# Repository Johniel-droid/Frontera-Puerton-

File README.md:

Perspectiva del proyecto: FRONTERA será desarrollado como un proyecto con enfoque educativo, utilizando un portón automatizado como ejemplo práctico para aprender y aplicar conceptos de programación, máquinas de estados, control de motores y comunicación Wi-Fi. El sistema permitirá observar de manera práctica cómo interactúan el microcontrolador, sensores, actuadores y comunicación inalámbrica.

El Estudiante tendra el sentir de que esta aplicando inmediatamente lo que aprende.

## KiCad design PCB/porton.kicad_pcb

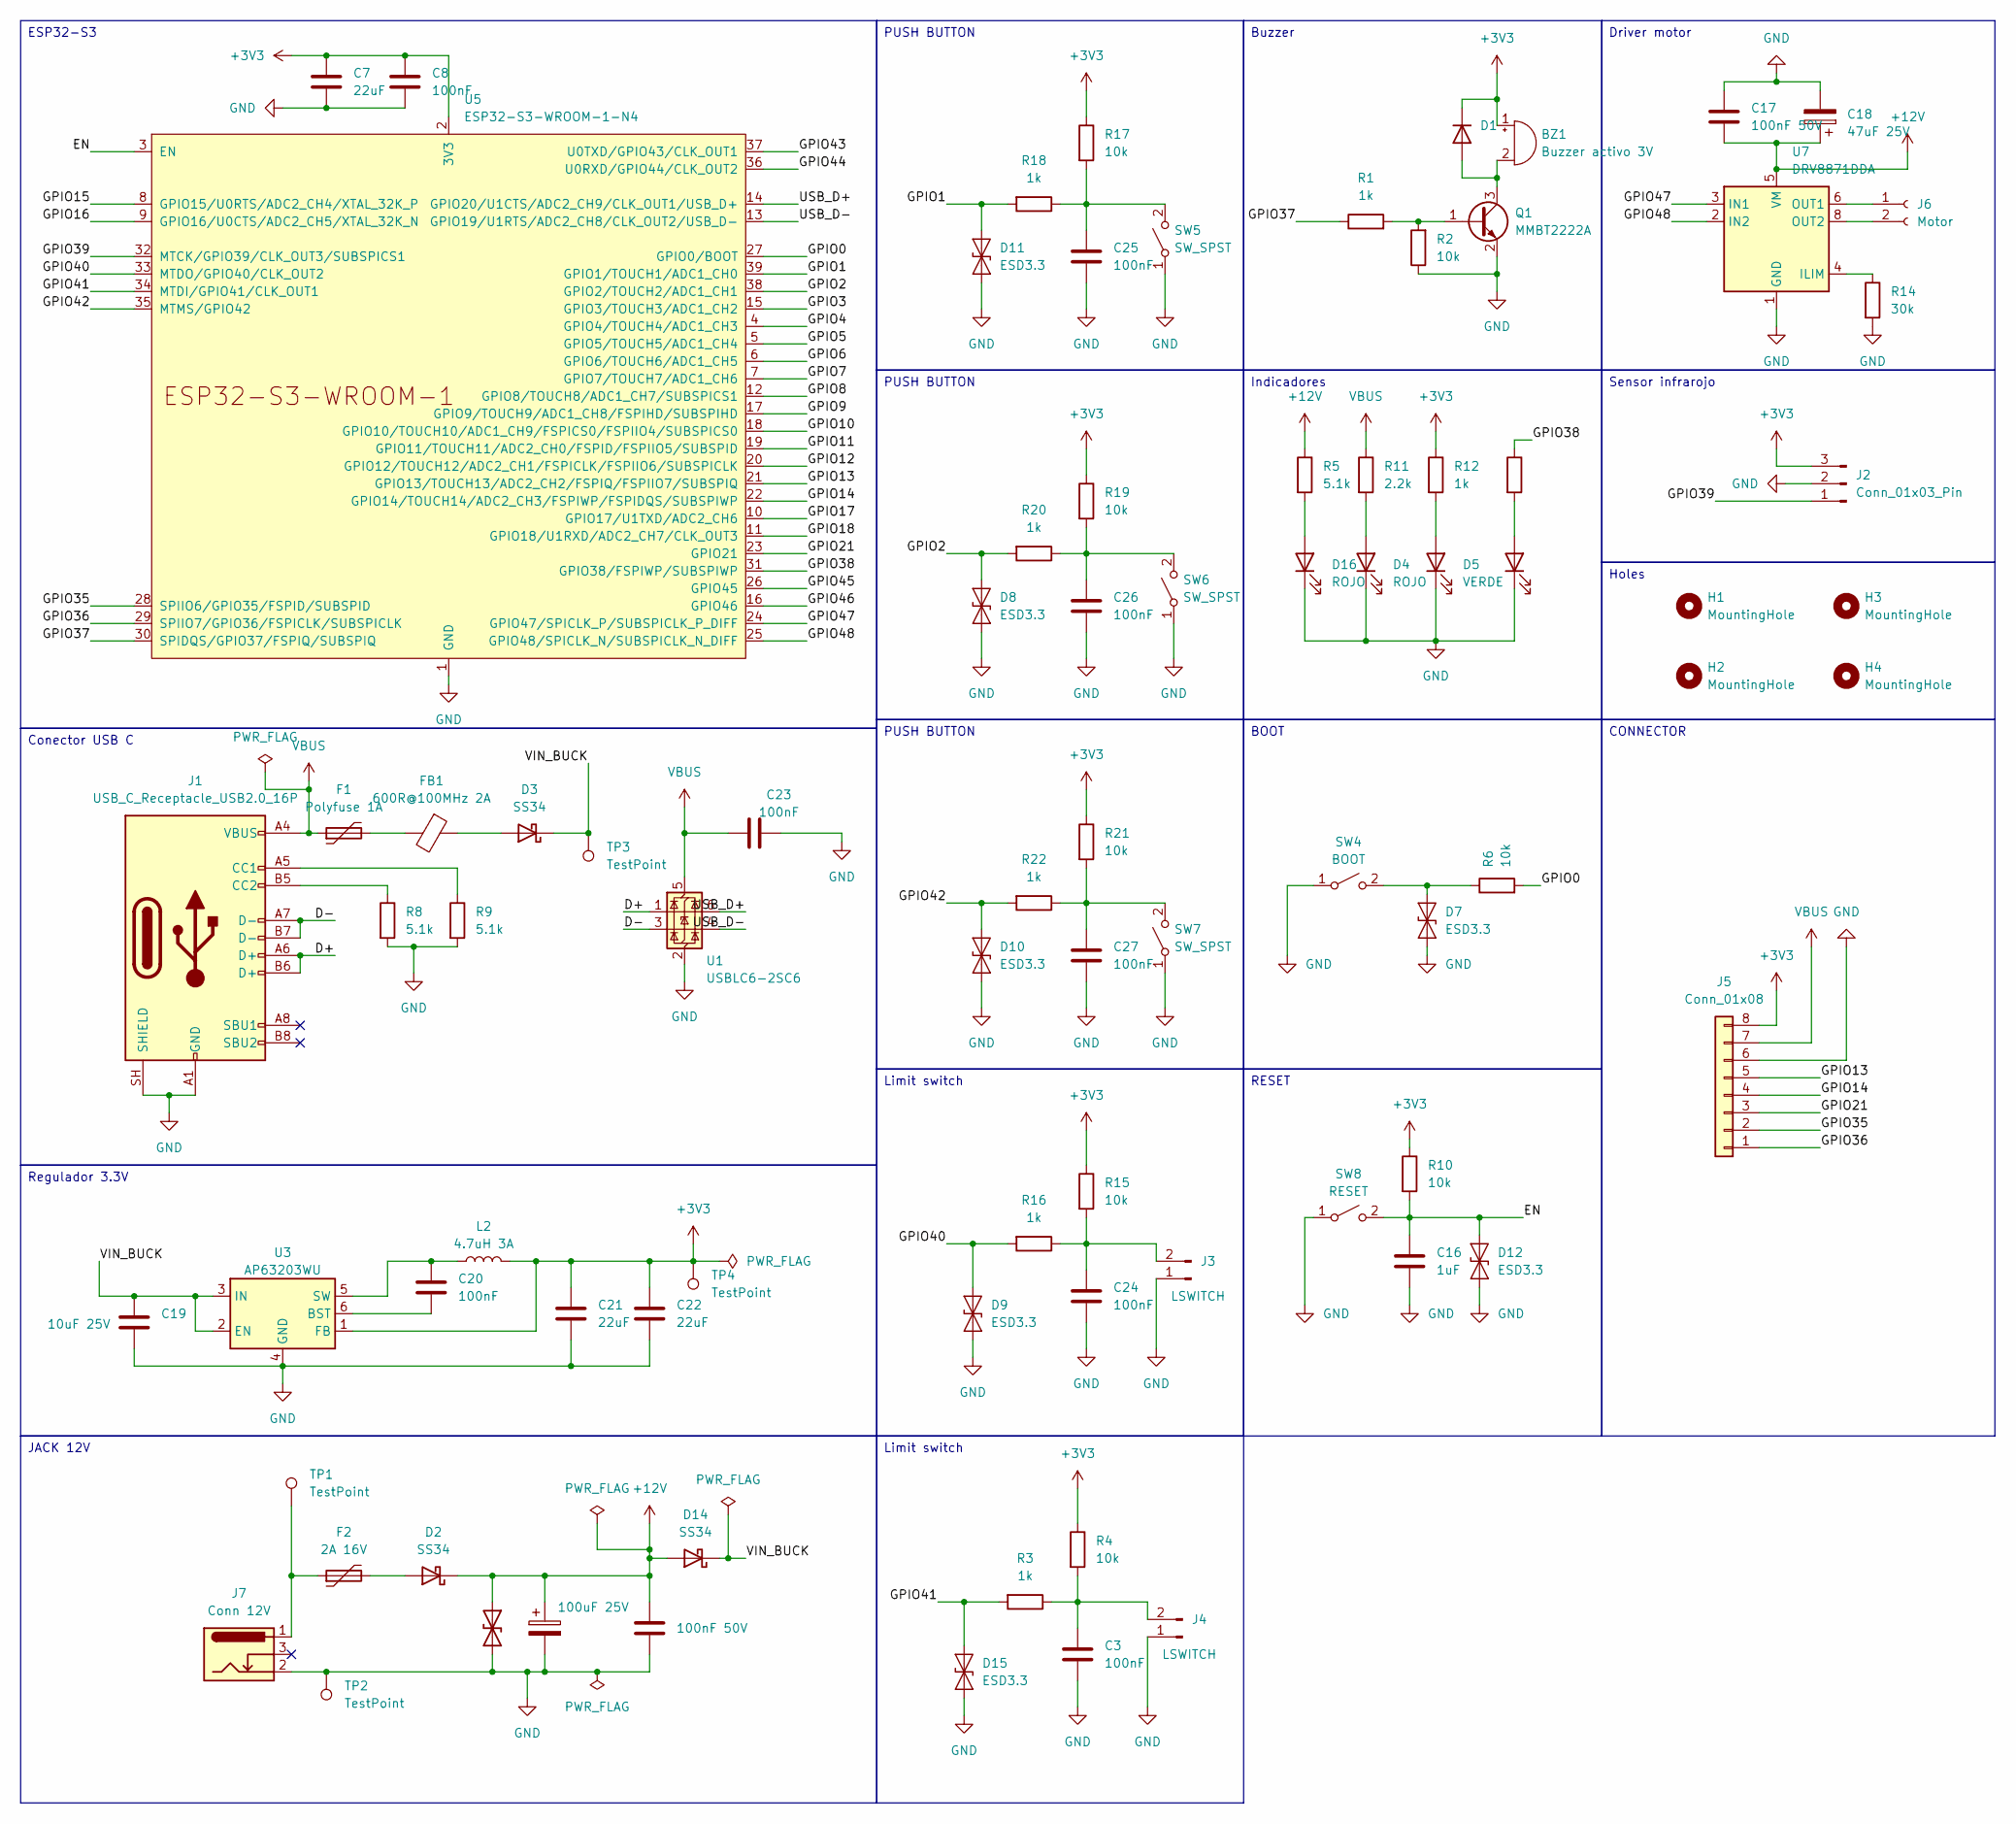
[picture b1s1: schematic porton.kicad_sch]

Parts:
BZ1: Buzzer activo 3V; Buzzer_12x9.5RM7.6; LCSC C252940
C1: 100uF 25V; CP_Elec_6.3x7.7; LCSC C3008501
C2: 100nF 50V; C_0805_2012Metric; LCSC C49678
C3, C8, C20, C24, C25, C26, C27: 100nF; C_0603_1608Metric; LCSC C14663
C7, C21, C22: 22uF; C_0805_2012Metric; LCSC C45783
C16: 1uF; C_0805_2012Metric; LCSC C28323
C17: 100nF 50V; C_0603_1608Metric; LCSC C14663
C18: 47uF 25V; CP_Elec_6.3x5.4; LCSC C2935117
C19: 10uF 25V; C_0805_2012Metric; LCSC C15850
C23: 100nF; C_0805_2012Metric; LCSC C49678
D1: 1N4148W; D_SOD-123; LCSC C81598
D2, D3, D14: SS34; D_SMA; LCSC C8678
D4, D16: ROJO; LED_0603_1608Metric; LCSC C2286
D5: VERDE; LED_0603_1608Metric; LCSC C72043
D6: Amarillo; LED_0603_1608Metric; LCSC C72038
D7, D8, D9, D10, D11, D12, D15: ESD3.3; D_SOD-923; LCSC C96512
D13: SMBJ15CA; D_SMB; LCSC C113989
F1: Polyfuse 1A; Fuse_1206_3216Metric; LCSC C883131
F2: 2A 16V; Fuse_1812_4532Metric; LCSC C18198340
FB1: 600R@100MHz 2A; L_0805_2012Metric; LCSC C21519
H1, H2, H3, H4: MountingHole; MountingHole_3.2mm_M3
J1: USB_C_Receptacle_USB2.0_16P; USB_C_Receptacle_HRO_TYPE-C-31-M-12; LCSC C165948
J2: Conn_01x03_Pin; JST_XH_B3B-XH-A_1x03_P2.50mm_Vertical; LCSC C144394
J3, J4: LSWITCH; JST_XH_B2B-XH-A_1x02_P2.50mm_Vertical; LCSC C158012
J5: Conn_01x08; PinHeader_1x08_P2.54mm_Vertical
J6: Motor; TerminalBlock_Phoenix_MKDS-1,5-2-5.08_1x02_P5.08mm_Horizont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
J7: Conn 12V; BarrelJack_Horizontal
L2: 4.7uH 3A; L_Taiyo-Yuden_NR-50xx; LCSC C223064
Q1: MMBT2222A; SOT-23; LCSC C8512
R1, R3, R12, R13, R16, R18, R20, R22: 1k; R_0603_1608Metric; LCSC C21190
R2, R4, R6, R10, R15, R17, R19, R21: 10k; R_0603_1608Metric; LCSC C25804
R5, R8, R9: 5.1k; R_0603_1608Metric; LCSC C23186
R11: 2.2k; R_0603_1608Metric; LCSC C4190
R14: 30k; R_0603_1608Metric; LCSC C22984
SW4: BOOT; SW_SPST_B3U-1000P; LCSC C231329
SW5, SW6, SW7: SW_SPST; SW_SPST_B3U-1000P; LCSC C231329
SW8: RESET; SW_SPST_B3U-1000P; LCSC C231329
TP1, TP2, TP3, TP4: TestPoint; TestPoint_Pad_D2.0mm
U1: USBLC6-2SC6; SOT-23-6; LCSC C7519
U3: AP63203WU; TSOT-23-6; LCSC C780769
U5: ESP32-S3-WROOM-1-N4; ESP32-S3-WROOM-1; LCSC C2913197
U7: DRV8871DDA; Texas_HTSOP-8-1EP_3.9x4.9mm_P1.27mm_EP2.95x4.9mm_Mask2.4x3.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; LCSC C75864

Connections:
+3V3: BZ1.1 (+), C7.1, C8.1, C21.1, C22.1, D1.1 (K), J2.3, J5.8, L2.2, R4.1, R10.1, R12.1, R15.1, R17.1, R19.1, R21.1, TP4.1 (1_1), U3.1 (FB), U5.2 (3V3)
+12V: C1.1, C2.1, C17.2, C18.1, D2.1 (K), D13.1 (A1), D14.2 (A), R5.1, U7.5 (VM)
/D+: J1.A6 (D+), J1.B6 (D+), U1.1 (I/O1)
/D-: J1.A7 (D-), J1.B7 (D-), U1.3 (I/O2)
/EN: C16.2, D12.2 (A2), R10.2, SW8.2 (B), U5.3 (EN)
/GPIO0: R6.2, U5.27 (GPIO0/BOOT)
/GPIO1: D11.2 (A2), R18.2, U5.39 (GPIO1/TOUCH1/ADC1_CH0)
/GPIO2: D8.2 (A2), R20.2, U5.38 (GPIO2/TOUCH2/ADC1_CH1)
/GPIO3: U5.15 (GPIO3/TOUCH3/ADC1_CH2)
/GPIO4: U5.4 (GPIO4/TOUCH4/ADC1_CH3)
/GPIO5: U5.5 (GPIO5/TOUCH5/ADC1_CH4)
/GPIO6: U5.6 (GPIO6/TOUCH6/ADC1_CH5)
/GPIO7: U5.7 (GPIO7/TOUCH7/ADC1_CH6)
/GPIO8: U5.12 (GPIO8/TOUCH8/ADC1_CH7/SUBSPICS1)
/GPIO9: U5.17 (GPIO9/TOUCH9/ADC1_CH8/FSPIHD/SUBSPIHD)
/GPIO10: U5.18 (GPIO10/TOUCH10/ADC1_CH9/FSPICS0/FSPIIO4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)
/GPIO11: U5.19 (GPIO11/TOUCH11/ADC2_CH0/FSPID/FSPIIO5/S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)
/GPIO12: U5.20 (GPIO12/TOUCH12/ADC2_CH1/FSPICLK/FSPIIO6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)
/GPIO13: J5.5, U5.21 (GPIO13/TOUCH13/ADC2_CH2/FSPIQ/FSPIIO7/S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)
/GPIO14: J5.4, U5.22 (GPIO14/TOUCH14/ADC2_CH3/FSPIWP/FSPIDQS/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)
/GPIO15: U5.8 (GPIO15/U0RTS/ADC2_CH4/XTAL_32K_P)
/GPIO16: U5.9 (GPIO16/U0CTS/ADC2_CH5/XTAL_32K_N)
/GPIO17: U5.10 (GPIO17/U1TXD/ADC2_CH6)
/GPIO18: U5.11 (GPIO18/U1RXD/ADC2_CH7/CLK_OUT3)
/GPIO21: J5.3, U5.23 (GPIO21)
/GPIO35: J5.2, U5.28 (SPIIO6/GPIO35/FSPID/SUBSPID)
/GPIO36: J5.1, U5.29 (SPIIO7/GPIO36/FSPICLK/SUBSPICLK)
/GPIO37: R1.1, U5.30 (SPIDQS/GPIO37/FSPIQ/SUBSPIQ)
/GPIO38: R13.1, U5.31 (GPIO38/FSPIWP/SUBSPIWP)
/GPIO39: J2.1, U5.32 (MTCK/GPIO39/CLK_OUT3/SUBSPICS1)
/GPIO40: D9.2 (A2), R16.2, U5.33 (MTDO/GPIO40/CLK_OUT2)
/GPIO41: D15.2 (A2), R3.2, U5.34 (MTDI/GPIO41/CLK_OUT1)
/GPIO42: D10.2 (A2), R22.2, U5.35 (MTMS/GPIO42)
/GPIO43: U5.37 (U0TXD/GPIO43/CLK_OUT1)
/GPIO44: U5.36 (U0RXD/GPIO44/CLK_OUT2)
/GPIO45: U5.26 (GPIO45)
/GPIO46: U5.16 (GPIO46)
/GPIO47: U5.24 (GPIO47/SPICLK_P/SUBSPICLK_P_DIFF), U7.3 (IN1)
/GPIO48: U5.25 (GPIO48/SPICLK_N/SUBSPICLK_N_DIFF), U7.2 (IN2)
/USB_D+: U1.6 (I/O1), U5.14 (GPIO20/U1CTS/ADC2_CH9/CLK_OUT1/USB_D+)
/USB_D-: U1.4 (I/O2), U5.13 (GPIO19/U1RTS/ADC2_CH8/CLK_OUT2/USB_D-)
/VIN_BUCK: C19.1, D3.1 (K), D14.1 (K), TP3.1 (1_1), U3.2 (EN), U3.3 (IN)
GND: C1.2, C2.2, C3.2, C7.2, C8.2, C16.1, C17.1, C18.2, C19.2, C21.2, C22.2, C23.1, C24.2, C25.2, C26.2, C27.2, D4.1 (K), D5.1 (K), D6.1 (K), D7.1 (A1), D8.1 (A1), D9.1 (A1), D10.1 (A1), D11.1 (A1), D12.1 (A1), D13.2 (A2), D15.1 (A1), D16.1 (K), J1.A1 (GND), J1.A12 (GND), J1.B1 (GND), J1.B12 (GND), J1.SH (SHIELD), J2.2, J3.1, J4.1, J5.6, J7.2, Q1.2 (E), R2.1, R8.2, R9.2, R14.2, SW4.1 (A), SW5.1 (A), SW6.1 (A), SW7.1 (A), SW8.1 (A), TP2.1 (1_1), U1.2 (GND), U3.4 (GND), U5.1 (GND), U5.40 (GND), U5.41 (GND), U7.1 (GND), U7.7 (GND), U7.9 (GND)
unnamed: BZ1.2 (-), D1.2 (A), Q1.3 (C)
unnamed: D2.2 (A), F2.2
unnamed: D3.2 (A), FB1.1
unnamed: D4.2 (A), R11.2
unnamed: D5.2 (A), R12.2
unnamed: D6.2 (A), R13.2
unnamed: D7.2 (A2), R6.1, SW4.2 (B)
unnamed: D16.2 (A), R5.2
unnamed: F1.2, FB1.2
unnamed: F2.1, J7.1, TP1.1 (1_1)
unnamed: J1.A5 (CC1), R9.1
unnamed: J1.B5 (CC2), R8.1
unnamed: C24.1, J3.2, R15.2, R16.1
unnamed: C3.1, J4.2, R3.1, R4.2
unnamed: J6.1, U7.6 (OUT1)
unnamed: J6.2, U7.8 (OUT2)
unnamed: Q1.1 (B), R1.2, R2.2
unnamed: C25.1, R17.2, R18.1, SW5.2 (B)
unnamed: C26.1, R19.2, R20.1, SW6.2 (B)
unnamed: C27.1, R21.2, R22.1, SW7.2 (B)
unnamed: C20.2, U3.6 (BST)
unnamed: C20.1, L2.1, U3.5 (SW)
unnamed: R14.1, U7.4 (ILIM)
VBUS: C23.2, F1.1, J1.A4 (VBUS), J1.A9 (VBUS), J1.B4 (VBUS), J1.B9 (VBUS), J5.7, R11.1, U1.5 (VBUS)

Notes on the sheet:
RESET
Indicadores
ESP32-S3
CONNECTOR
Driver motor
Limit switch
Sensor infrarojo
PUSH BUTTON
Holes
Conector USB C
Buzzer
JACK 12V
BOOT
Regulador 3.3V

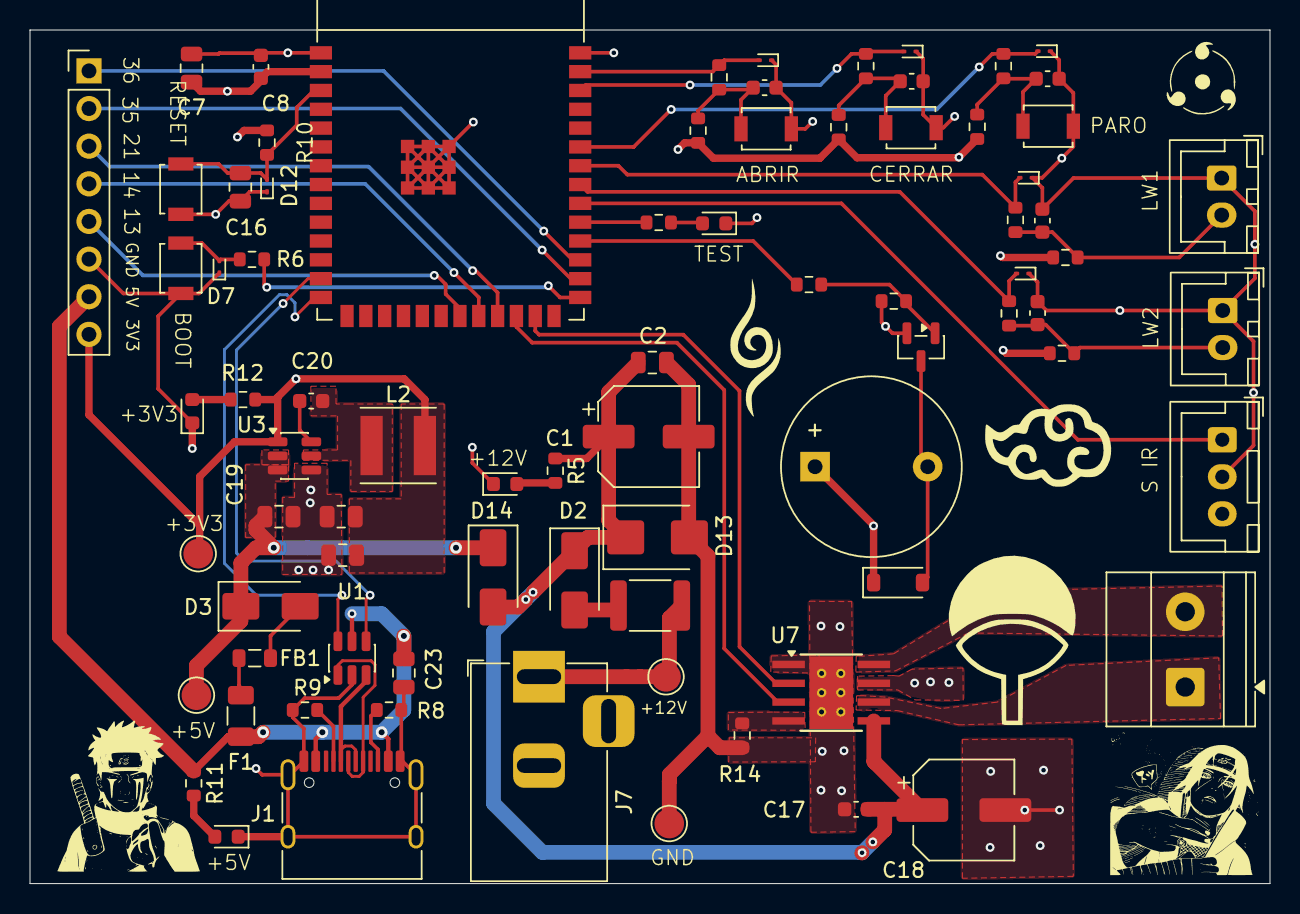
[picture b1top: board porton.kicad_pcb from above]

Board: 4 copper layers, 83.7 x 57.6 mm, 80 parts (0 on the bottom side), 49 nets.

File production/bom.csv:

Designator,Footprint,Quantity,Value,LCSC Part #
C1,CP_Elec_6.3x7.7,1,100uF 25V,C3008501
C16,0805,1,1uF,C28323
C17,0603,1,100nF 50V,C14663
C18,CP_Elec_6.3x5.4,1,47uF 25V,C2935117
C19,0805,1,10uF 25V,C15850
C2,0805,1,100nF 50V,C49678
"C20, C24, C25, C26, C27, C3, C8",0603,7,100nF,C14663
"C21, C22, C7",0805,3,22uF,C45783
C23,0805,1,100nF,C49678
D1,D_SOD-123,1,1N4148W,C81598
"D10, D11, D12, D15, D7, D8, D9",D_SOD-923,7,ESD3.3,C96512
D13,D_SMB,1,SMBJ15CA,C113989
"D14, D2, D3",D_SMA,3,SS34,C8678
"D16, D4",0603,2,ROJO,C2286
D5,0603,1,VERDE,C72043
D6,0603,1,Amarillo,C72038
F1,1206,1,Polyfuse 1A,C883131
F2,1812,1,2A 16V,C18198340
FB1,0805,1,600R@100MHz 2A,C21519
J1,USB_C_Receptacle_HRO_TYPE-C-31-M-12,1,USB_C_Receptacle_USB2.0_16P,C165948
L2,L_Taiyo-Yuden_NR-50xx,1,4.7uH 3A,C223064
Q1,SOT-23,1,MMBT2222A,C8512
"R1, R12, R13, R16, R18, R20, R22, R3",0603,8,1k,C21190
"R10, R15, R17, R19, R2, R21, R4, R6",0603,8,10k,C25804
R11,0603,1,2.2k,C4190
R14,0603,1,30k,C22984
"R5, R8, R9",0603,3,5.1k,C23186
SW4,SW_SPST_B3U-1000P,1,BOOT,C231329
"SW5, SW6, SW7",SW_SPST_B3U-1000P,3,SW_SPST,C231329
SW8,SW_SPST_B3U-1000P,1,RESET,C231329
U1,SOT-23-6,1,USBLC6-2SC6,C7519
U3,TSOT-23-6,1,AP63203WU,C780769
U5,ESP32-S3-WROOM-1,1,ESP32-S3-WROOM-1-N4,C2913197
U7,Texas_HTSOP-8-1EP_3.9x4.9mm_P1.27mm_EP2.95x4.9mm_Mask2.4x3.1mm_ThermalVias,1,DRV8871DDA,C75864

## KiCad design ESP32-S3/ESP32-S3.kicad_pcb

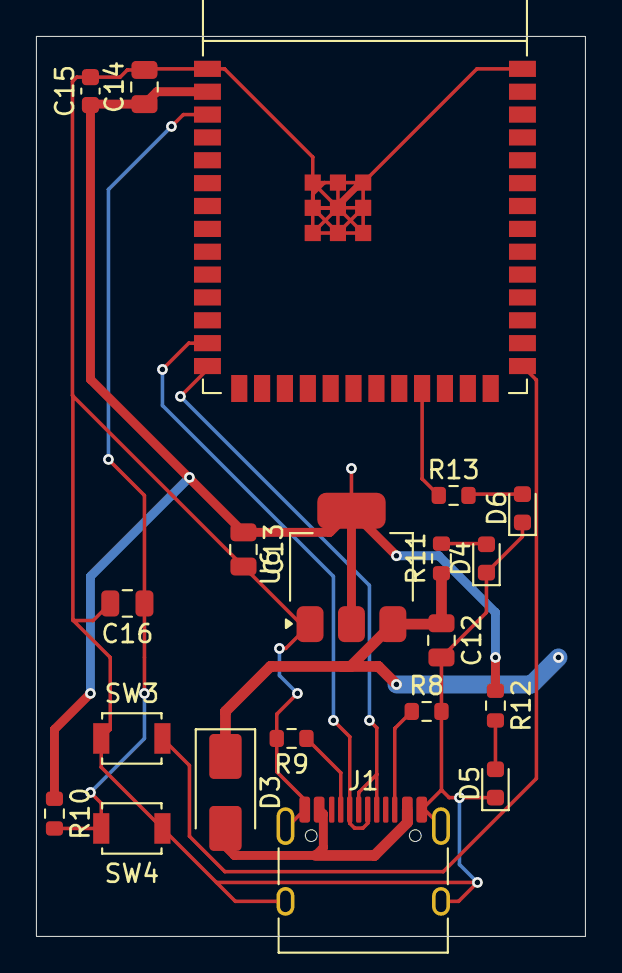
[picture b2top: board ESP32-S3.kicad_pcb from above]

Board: 2 copper layers, 30.5 x 50.0 mm, 20 parts (0 on the bottom side), 14 nets.

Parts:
C12: 10uF; C_0805_2012Metric
C13, C14: 22uF; C_0805_2012Metric
C15: 100nF; C_0603_1608Metric
C16: 10uf; C_0805_2012Metric
D3: D_Schottky; D_SMA
D4: ROJO; LED_0603_1608Metric
D5: VERDE; LED_0603_1608Metric
D6: AZUL; LED_0603_1608Metric
J1: USB_C_Receptacle_USB2.0_16P; USB_C_Receptacle_HRO_TYPE-C-31-M-12
R8: 5.1kΩ; R_0603_1608Metric
R9: 5.1 kΩ; R_0603_1608Metric
R10: 5.1K; R_0603_1608Metric
R11, R12, R13: 5.1k; R_0603_1608Metric
SW3, SW4: SW_SPST; SW_SPST_B3U-1000P
U5: ESP32-S3-WROOM-1
U6: LD1117S33TR_SOT223; SOT-223-3_TabPin2

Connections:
+3V3: C13.1, C14.1, C15.1, R10.1, R12.1, U5.2 (3V3), U6.2 (VO)
+5V: C12.1, D3.1 (K), R11.1, U6.3 (VI)
/D+: J1.A6 (D+), J1.B6 (D+), U5.14 (GPIO20/U1CTS/ADC2_CH9/CLK_OUT1/USB_D+)
/D-: J1.A7 (D-), J1.B7 (D-), U5.13 (GPIO19/U1RTS/ADC2_CH8/CLK_OUT2/USB_D-)
/EN: C16.1, R10.2, SW4.2 (B), U5.3 (EN)
/GPIO0: SW3.2 (B), U5.27 (GPIO0/BOOT)
/GPIO21: R13.1, U5.23 (GPIO21)
GND: C12.2, C13.2, C14.2, C15.2, C16.2, D4.1 (K), D5.1 (K), D6.1 (K), J1.A1 (GND), J1.A12 (GND), J1.B1 (GND), J1.B12 (GND), J1.SH (SHIELD), R8.2, R9.2, SW3.1 (A), SW4.1 (A), U5.1 (GND), U5.40 (GND), U5.41 (GND), U6.1 (GND)
unnamed: D3.2 (A), J1.A4 (VBUS), J1.A9 (VBUS), J1.B4 (VBUS), J1.B9 (VBUS)
unnamed: D4.2 (A), R11.2
unnamed: D5.2 (A), R12.2
unnamed: D6.2 (A), R13.2
unnamed: J1.A5 (CC1), R9.1
unnamed: J1.B5 (CC2), R8.1

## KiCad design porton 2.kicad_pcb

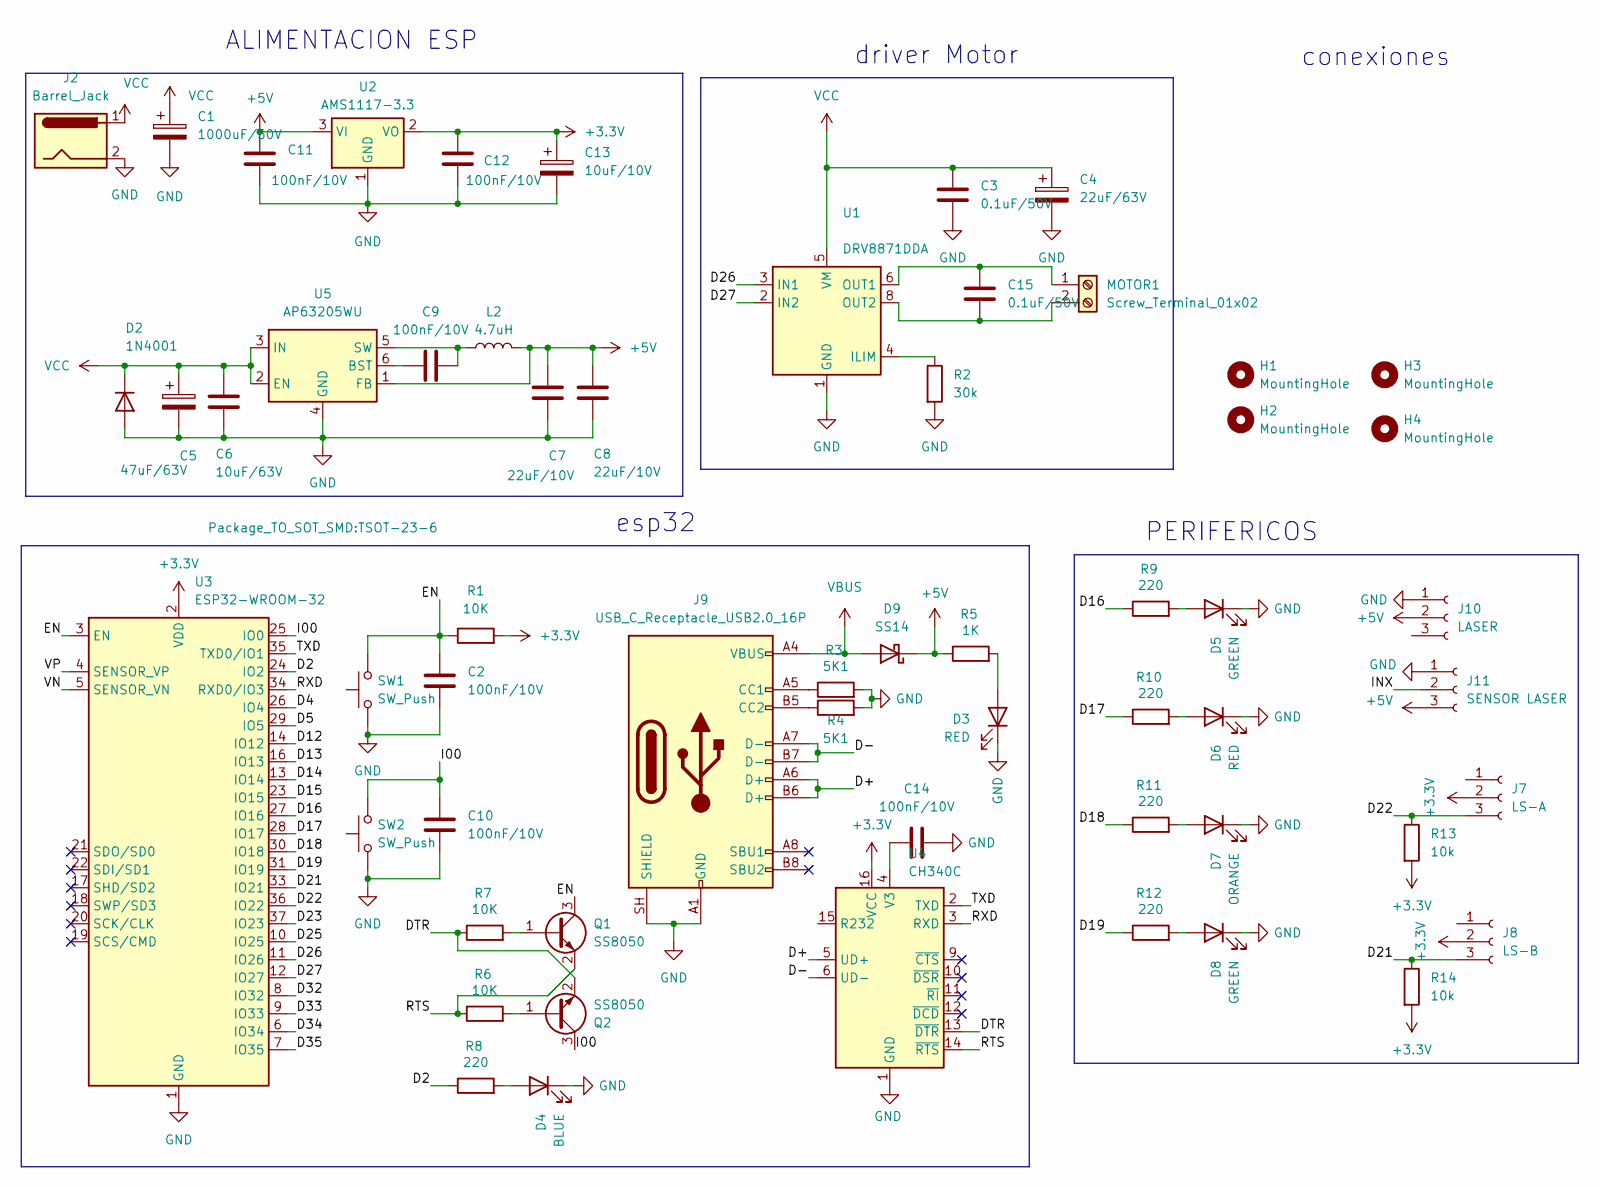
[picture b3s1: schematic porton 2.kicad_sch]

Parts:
C1: 1000uF/50V; CP_Elec_6.3x7.7
C2, C9, C10, C11, C12, C14: 100nF/10V; C_0805_2012Metric
C3, C15: 0.1uF/50V; C_0805_2012Metric
C4: 22uF/63V; CP_Elec_6.3x7.7
C5: 47uF/63V; CP_Elec_6.3x7.7
C6: 10uF/63V; C_0805_2012Metric
C7, C8: 22uF/10V; C_0805_2012Metric
C13: 10uF/10V; CP_EIA-3528-21_Kemet-B_HandSolder
D2: 1N4001; D_SMA_Handsoldering
D3, D6: RED; LED_1206_3216Metric
D4: BLUE; LED_1206_3216Metric
D5, D8: GREEN; LED_1206_3216Metric
D7: ORANGE; LED_1206_3216Metric
D9: SS14; D_SMA
H1, H2, H3, H4: MountingHole; MountingHole_2.5mm
J2: Barrel_Jack; BarrelJack_GCT_DCJ200-10-A_Horizontal
J7: LS-A; JST_PH_B3B-PH-K_1x03_P2.00mm_Vertical
J8: LS-B; JST_PH_B3B-PH-K_1x03_P2.00mm_Vertical
J9: USB_C_Receptacle_USB2.0_16P; USB_C_Receptacle_Amphenol_12401948E412A
J10: LASER; JST_PH_B3B-PH-K_1x03_P2.00mm_Vertical
J11: SENSOR LASER; JST_PH_B3B-PH-K_1x03_P2.00mm_Vertical
L2: 4.7uH; L_Chilisin_BMRB00050518-B
MOTOR1: Screw_Terminal_01x02; TerminalBlock_MaiXu_MX126-5.0-02P_1x02_P5.00mm
Q1, Q2: SS8050; SOT-23
R1, R6, R7: 10K; R_0805_2012Metric_Pad1.20x1.40mm_HandSolder
R2: 30k; R_0805_2012Metric_Pad1.20x1.40mm_HandSolder
R3, R4: 5K1; R_0805_2012Metric_Pad1.20x1.40mm_HandSolder
R5: 1K; R_0805_2012Metric_Pad1.20x1.40mm_HandSolder
R8, R9, R10, R11, R12: 220; R_0805_2012Metric_Pad1.20x1.40mm_HandSolder
R13, R14: 10k; R_0805_2012Metric_Pad1.20x1.40mm_HandSolder
SW1, SW2: SW_Push; SW_Tactile_SPST_NO_Straight_CK_PTS636Sx25SMTRLFS
U1: DRV8871DDA; Texas_HTSOP-8-1EP_3.9x4.9mm_P1.27mm_EP2.95x4.9mm_Mask2.4x3.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
U2: AMS1117-3.3; SOT-223-3_TabPin2; lcsc C6186
U3: ESP32-WROOM-32; lcsc C701341
U4: CH340C; SOIC-16_3.9x9.9mm_P1.27mm
U5: AP63205WU; TSOT-23-6

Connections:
+3.3V: C12.2, C13.1, J7.2, J8.2, R1.2, R13.2, R14.2, U2.2 (VO), U3.2 (VDD), U4.16 (VCC)
+5V: C7.1, C8.1, C11.2, D9.1 (K), J10.2, J11.3, L2.2, R5.1, U2.3 (VI), U5.1 (FB)
/D2: R8.1, U3.24 (IO2)
/D4: U3.26 (IO4)
/D5: U3.29 (IO5)
/D12: U3.14 (IO12)
/D13: U3.16 (IO13)
/D14: U3.13 (IO14)
/D15: U3.23 (IO15)
/D16: R9.1, U3.27 (IO16)
/D17: R10.1, U3.28 (IO17)
/D18: R11.1, U3.30 (IO18)
/D19: R12.1, U3.31 (IO19)
/D21: J8.3, R14.1, U3.33 (IO21)
/D22: J7.3, R13.1, U3.36 (IO22)
/D23: U3.37 (IO23)
/D25: U3.10 (IO25)
/D26: U1.3 (IN1), U3.11 (IO26)
/D27: U1.2 (IN2), U3.12 (IO27)
/D32: U3.8 (IO32)
/D33: U3.9 (IO33)
/D34: U3.6 (IO34)
/D35: U3.7 (IO35)
/D+: J9.A6 (D+), J9.B6 (D+), U4.5 (UD+)
/D-: J9.A7 (D-), J9.B7 (D-), U4.6 (UD-)
/DTR: Q2.2 (E), R7.1, U4.13 (~DTR)
/EN: C2.2, Q1.3 (C), R1.1, SW1.2, U3.3 (EN)
/I00: C10.2, Q2.3 (C), SW2.2, U3.25 (IO0)
/INX: J11.2
/RTS: Q1.2 (E), R6.1, U4.14 (~RTS)
/RXD: U3.34 (RXD0/IO3), U4.3 (RXD)
/TXD: U3.35 (TXD0/IO1), U4.2 (TXD)
/VN: U3.5 (SENSOR_VN)
/VP: U3.4 (SENSOR_VP)
GND: C1.2, C2.1, C3.2, C4.2, C5.2, C6.2, C7.2, C8.2, C10.1, C11.1, C12.1, C13.2, C14.1, D2.2 (A), D3.1 (K), D4.1 (K), D5.1 (K), D6.1 (K), D7.1 (K), D8.1 (K), J2.2, J9.A1 (GND), J9.A12 (GND), J9.B1 (GND), J9.B12 (GND), J9.SH (SHIELD), J10.1, J11.1, R2.2, R3.2, R4.2, SW1.1, SW2.1, U1.1 (GND), U1.7 (GND), U1.9 (GND), U2.1 (GND), U3.1 (GND), U3.15 (GND), U3.38 (GND), U3.39 (GND), U4.1 (GND), U5.4 (GND)
unnamed: D3.2 (A), R5.2
unnamed: D4.2 (A), R8.2
unnamed: D5.2 (A), R9.2
unnamed: D6.2 (A), R10.2
unnamed: D7.2 (A), R11.2
unnamed: D8.2 (A), R12.2
unnamed: J9.A5 (CC1), R3.1
unnamed: J9.B5 (CC2), R4.1
unnamed: C15.1, MOTOR1.1, U1.6 (OUT1)
unnamed: C15.2, MOTOR1.2, U1.8 (OUT2)
unnamed: Q1.1 (B), R7.2
unnamed: Q2.1 (B), R6.2
unnamed: R2.1, U1.4 (ILIM)
unnamed: C14.2, U4.4 (V3)
unnamed: C9.1, U5.6 (BST)
unnamed: C9.2, L2.1, U5.5 (SW)
VBUS: D9.2 (A), J9.A4 (VBUS), J9.A9 (VBUS), J9.B4 (VBUS), J9.B9 (VBUS)
VCC: C1.1, C3.1, C4.1, C5.1, C6.1, D2.1 (K), J2.1, U1.5 (VM), U5.2 (EN), U5.3 (IN)

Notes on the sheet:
ALIMENTACION ESP
driver Motor
PERIFERICOS
conexiones
esp32

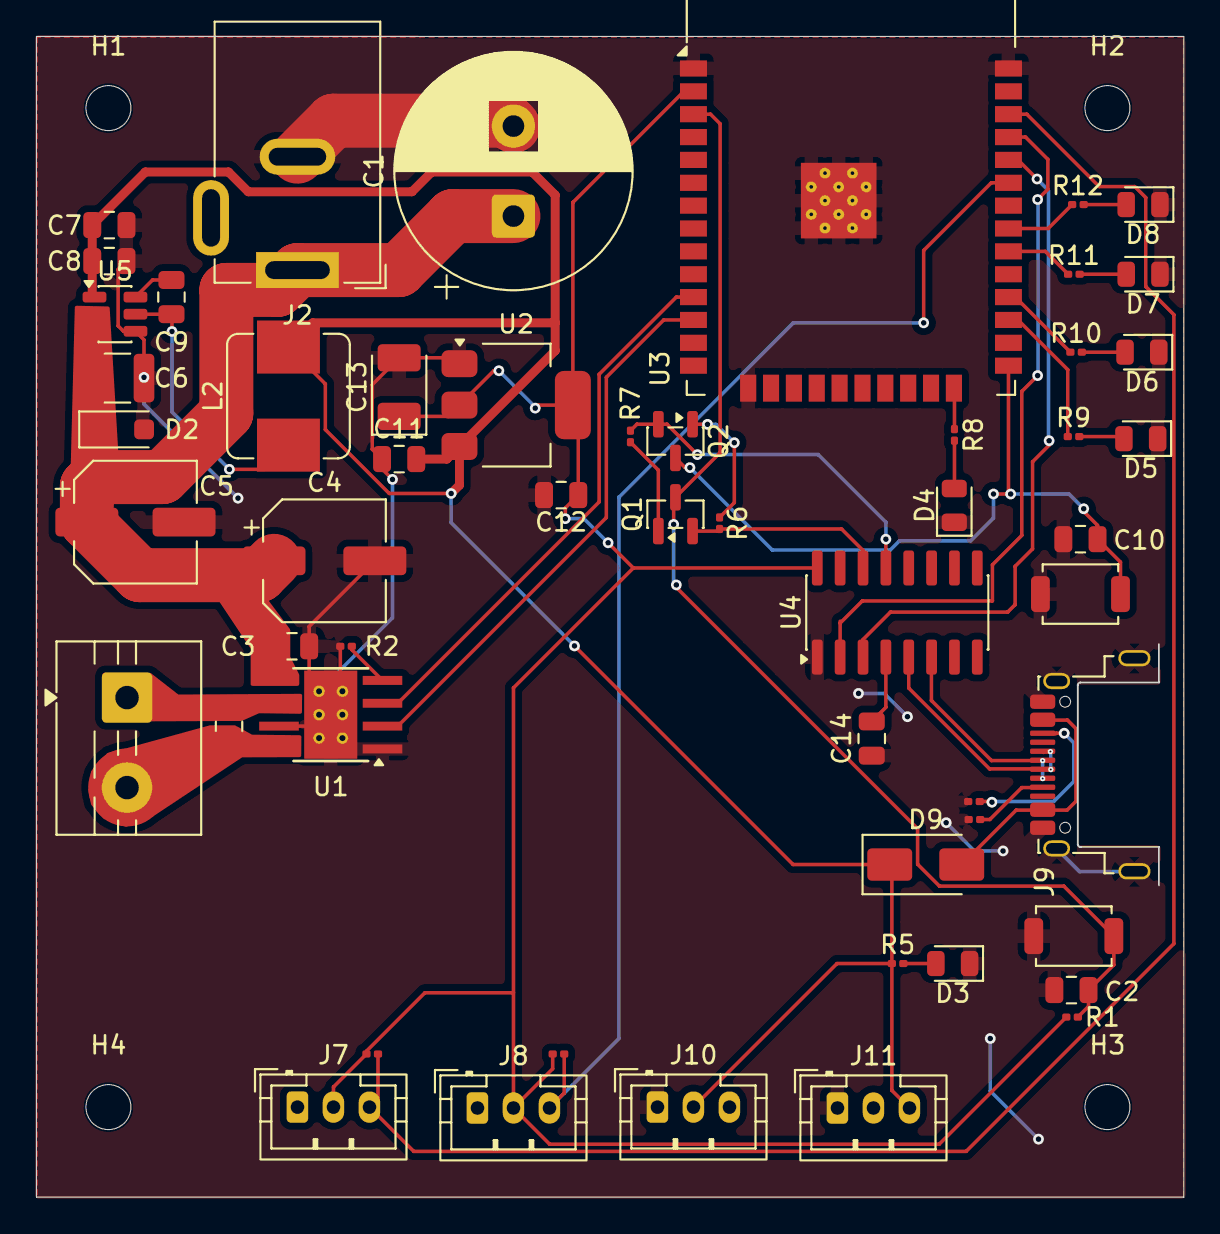
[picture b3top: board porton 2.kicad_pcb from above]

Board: 2 copper layers, 63.7 x 64.5 mm, 58 parts (0 on the bottom side), 38 nets.
